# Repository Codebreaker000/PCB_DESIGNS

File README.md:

# PCB_DESIGNS

Contains all PCB designs with Schematics and Board view file's and both pdf's to understand and gerber files and the view and layout of the PCB's.

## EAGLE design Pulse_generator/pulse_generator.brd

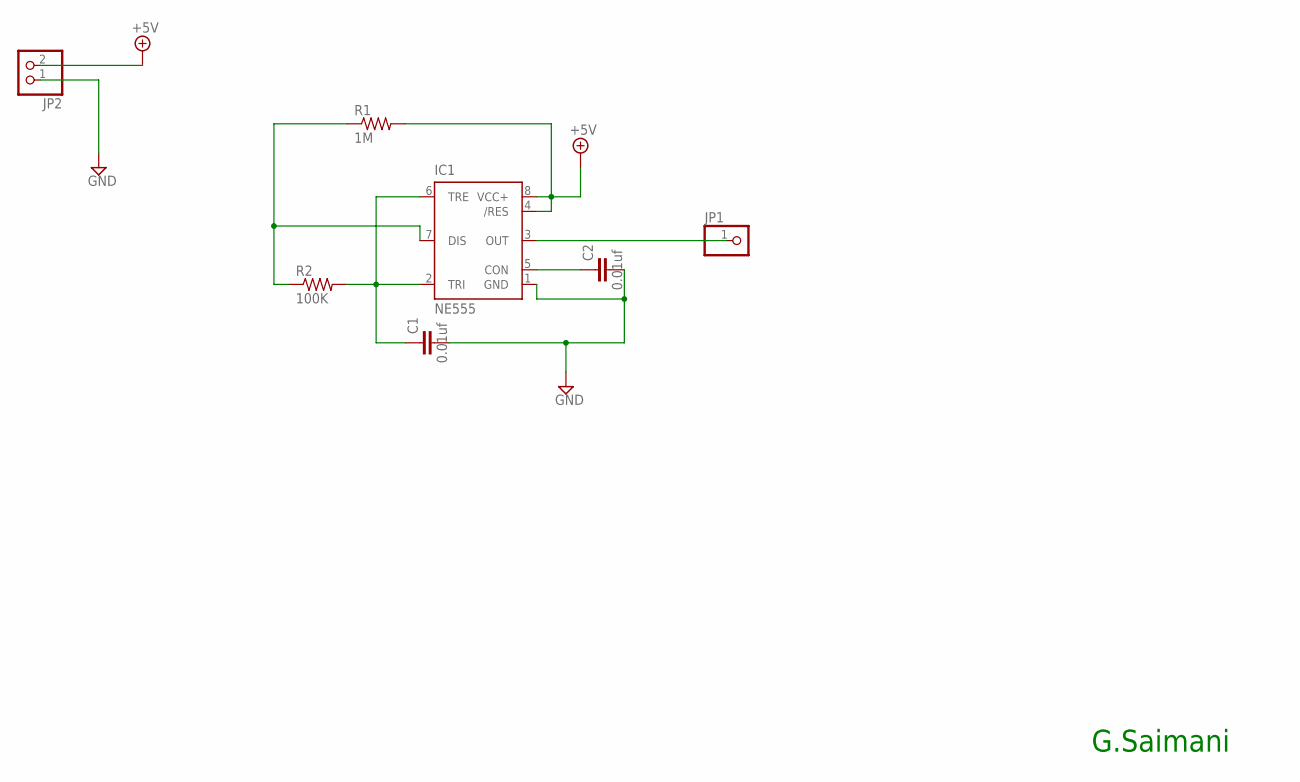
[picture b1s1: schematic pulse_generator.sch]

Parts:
C1, C2: 0.01uf; C050-024X044
IC1: NE555; DIL-08
JP1: PINHD-1X1; 1X01
JP2: PINHD-1X2; 1X02
R1: 1M; 0204/7
R2: 100K; 0204/7

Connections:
+5V: IC1.4 (/RES), IC1.8 (VCC+), JP2.2, R1.2
GND: C1.2, C2.2, IC1.1 (GND), JP2.1
unnamed: C1.1, IC1.2 (TRI), IC1.6 (TRE), R2.2
unnamed: IC1.3 (OUT), JP1.1
unnamed: IC1.7 (DIS), R1.1, R2.1
unnamed: C2.1, IC1.5 (CON)

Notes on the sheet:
G.Saimani

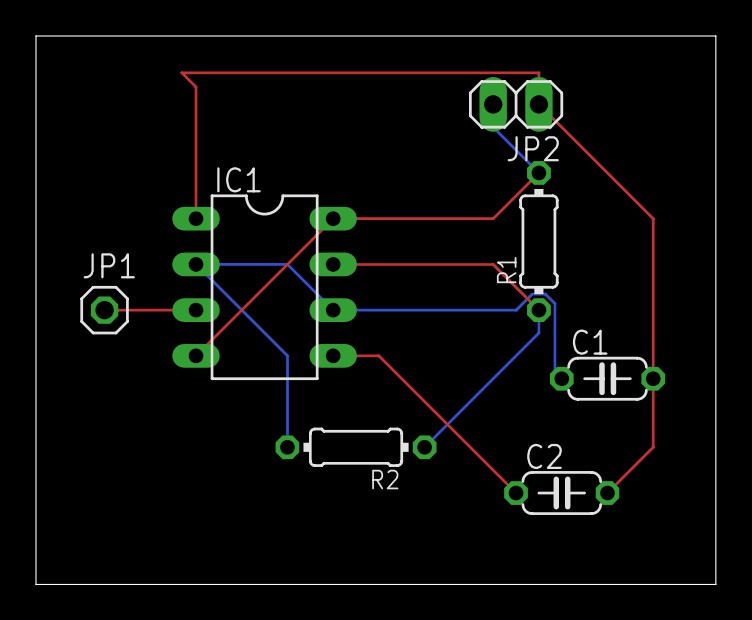
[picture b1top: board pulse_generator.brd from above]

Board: 2 copper layers, 37.8 x 30.5 mm, 7 parts (0 on the bottom side), 6 nets.

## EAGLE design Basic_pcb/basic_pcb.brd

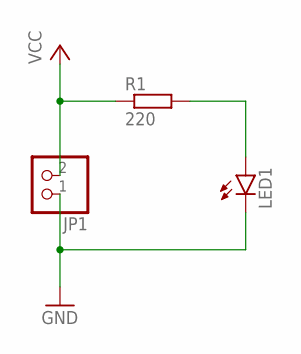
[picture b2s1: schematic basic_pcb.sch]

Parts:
JP1: PINHD-1X2; 1X02
LED1: LED3MM
R1: 220; 0204/7

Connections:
GND: JP1.1, LED1.K (C)
unnamed: LED1.A, R1.2
VCC: JP1.2, R1.1

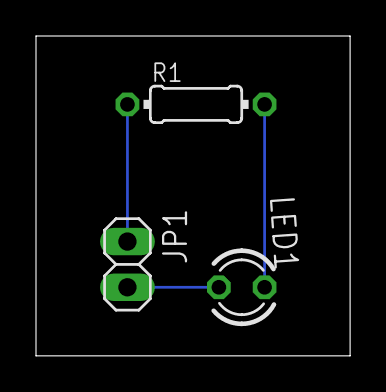
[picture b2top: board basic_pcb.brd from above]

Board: 2 copper layers, 17.4 x 17.8 mm, 3 parts (0 on the bottom side), 3 nets.

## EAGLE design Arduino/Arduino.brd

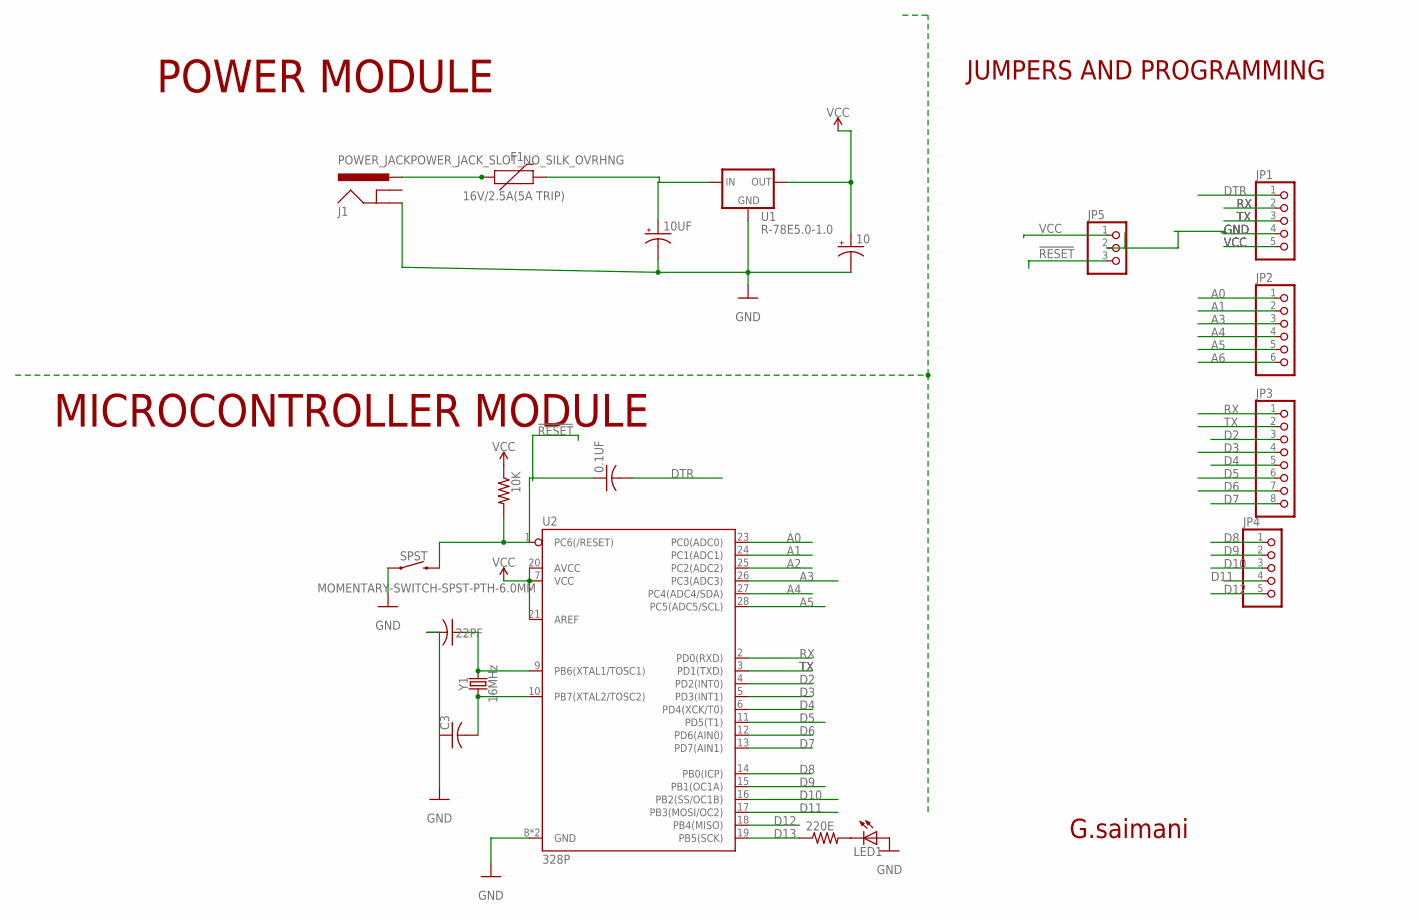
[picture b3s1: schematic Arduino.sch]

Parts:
0.1UF, 22PF: C-US025-024X044; C025-024X044
10, 10UF: CPOL-USE2-5; E2-5
10K: R-US_0204/7; 0204/7
220E: R-US_0207/7; 0207/7
C3: C-US025-024X044; C025-024X044
F1: 16V/2.5A(5A TRIP); 1812
J1: POWER_JACKPOWER_JACK_SLOT_NO_SILK_OVRHNG; POWER_JACK_PTH_SLOT_NO_OVRHNG_SILK
JP1, JP4: PINHD-1X5; 1X05
JP2: PINHD-1X6; 1X06
JP3: PINHD-1X8; 1X08
JP5: PINHD-1X3; 1X03
LED1: LED; SMARTLED-TTW
SPST: MOMENTARY-SWITCH-SPST-PTH-6.0MM; TACTILE_SWITCH_PTH_6.0MM
U1: R-78E5.0-1.0; DC-DC_CONVERTER_78XX
U2: 328P; DIP28
Y1: 16MHz; HC49US

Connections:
!RESET: JP5.3
A0: JP2.1, U2.23 (PC0(ADC0))
A1: JP2.2, U2.24 (PC1(ADC1))
A2: U2.25 (PC2(ADC2))
A3: JP2.3, U2.26 (PC3(ADC3))
A4: JP2.4, U2.27 (PC4(ADC4/SDA))
A5: JP2.5, U2.28 (PC5(ADC5/SCL))
A6: JP2.6
D2: JP3.3, U2.4 (PD2(INT0))
D3: JP3.4, U2.5 (PD3(INT1))
D4: JP3.5, U2.6 (PD4(XCK/T0))
D5: JP3.6, U2.11 (PD5(T1))
D6: JP3.7, U2.12 (PD6(AIN0))
D7: JP3.8, U2.13 (PD7(AIN1))
D8: JP4.1, U2.14 (PB0(ICP))
D9: JP4.2, U2.15 (PB1(OC1A))
D10: JP4.3, U2.16 (PB2(SS/OC1B))
D11: JP4.4, U2.17 (PB3(MOSI/OC2))
D12: JP4.5, U2.18 (PB4(MISO))
D13: 220E.1, U2.19 (PB5(SCK))
DTR: 0.1UF.2, JP1.1
GND: 10.-, 10UF.-, 22PF.2, C3.1, J1.GND, JP1.4, LED1.A@1 (A), SPST.1, U1.GND, U2.8 (GND), U2.22 (GND)
unnamed: 10UF.+, U1.VIN (IN)
unnamed: 22PF.1, U2.9 (PB6(XTAL1/TOSC1)), Y1.2
unnamed: C3.2, U2.10 (PB7(XTAL2/TOSC2)), Y1.1
unnamed: 0.1UF.1, 10K.2, SPST.3 (2), U2.1 (PC6(/RESET))
unnamed: 220E.2, LED1.C@1 (C)
unnamed: F1.1, J1.PWR
RX: JP1.2, JP3.1, U2.2 (PD0(RXD))
TX: JP1.3, JP3.2, U2.3 (PD1(TXD))
VCC: 10.+, 10K.1, JP1.5, JP5.1, U1.VOUT (OUT), U2.7 (VCC), U2.20 (AVCC), U2.21 (AREF)

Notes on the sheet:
POWER MODULE
MICROCONTROLLER MODULE
JUMPERS AND PROGRAMMING
G.saimani

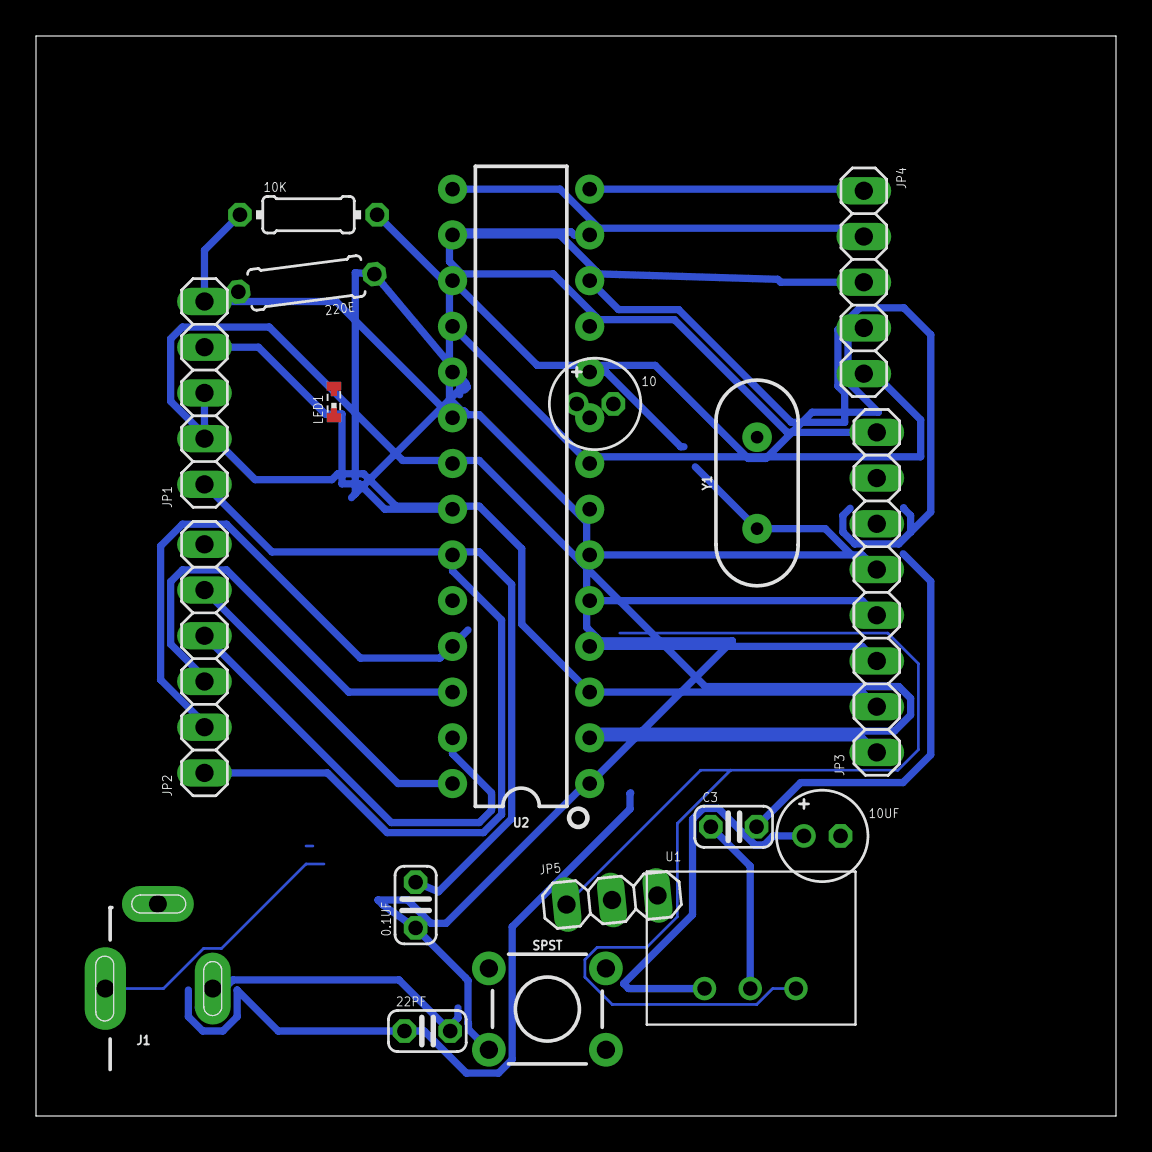
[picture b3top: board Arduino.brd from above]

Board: 2 copper layers, 60.0 x 60.0 mm, 19 parts (1 on the bottom side), 28 nets.

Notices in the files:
parts and their libraries:
SparkFun-Connectors: Licensing: Creative Commons ShareAlike 4.0 International - https://creativecommons.org/licenses/by-sa/4.0
